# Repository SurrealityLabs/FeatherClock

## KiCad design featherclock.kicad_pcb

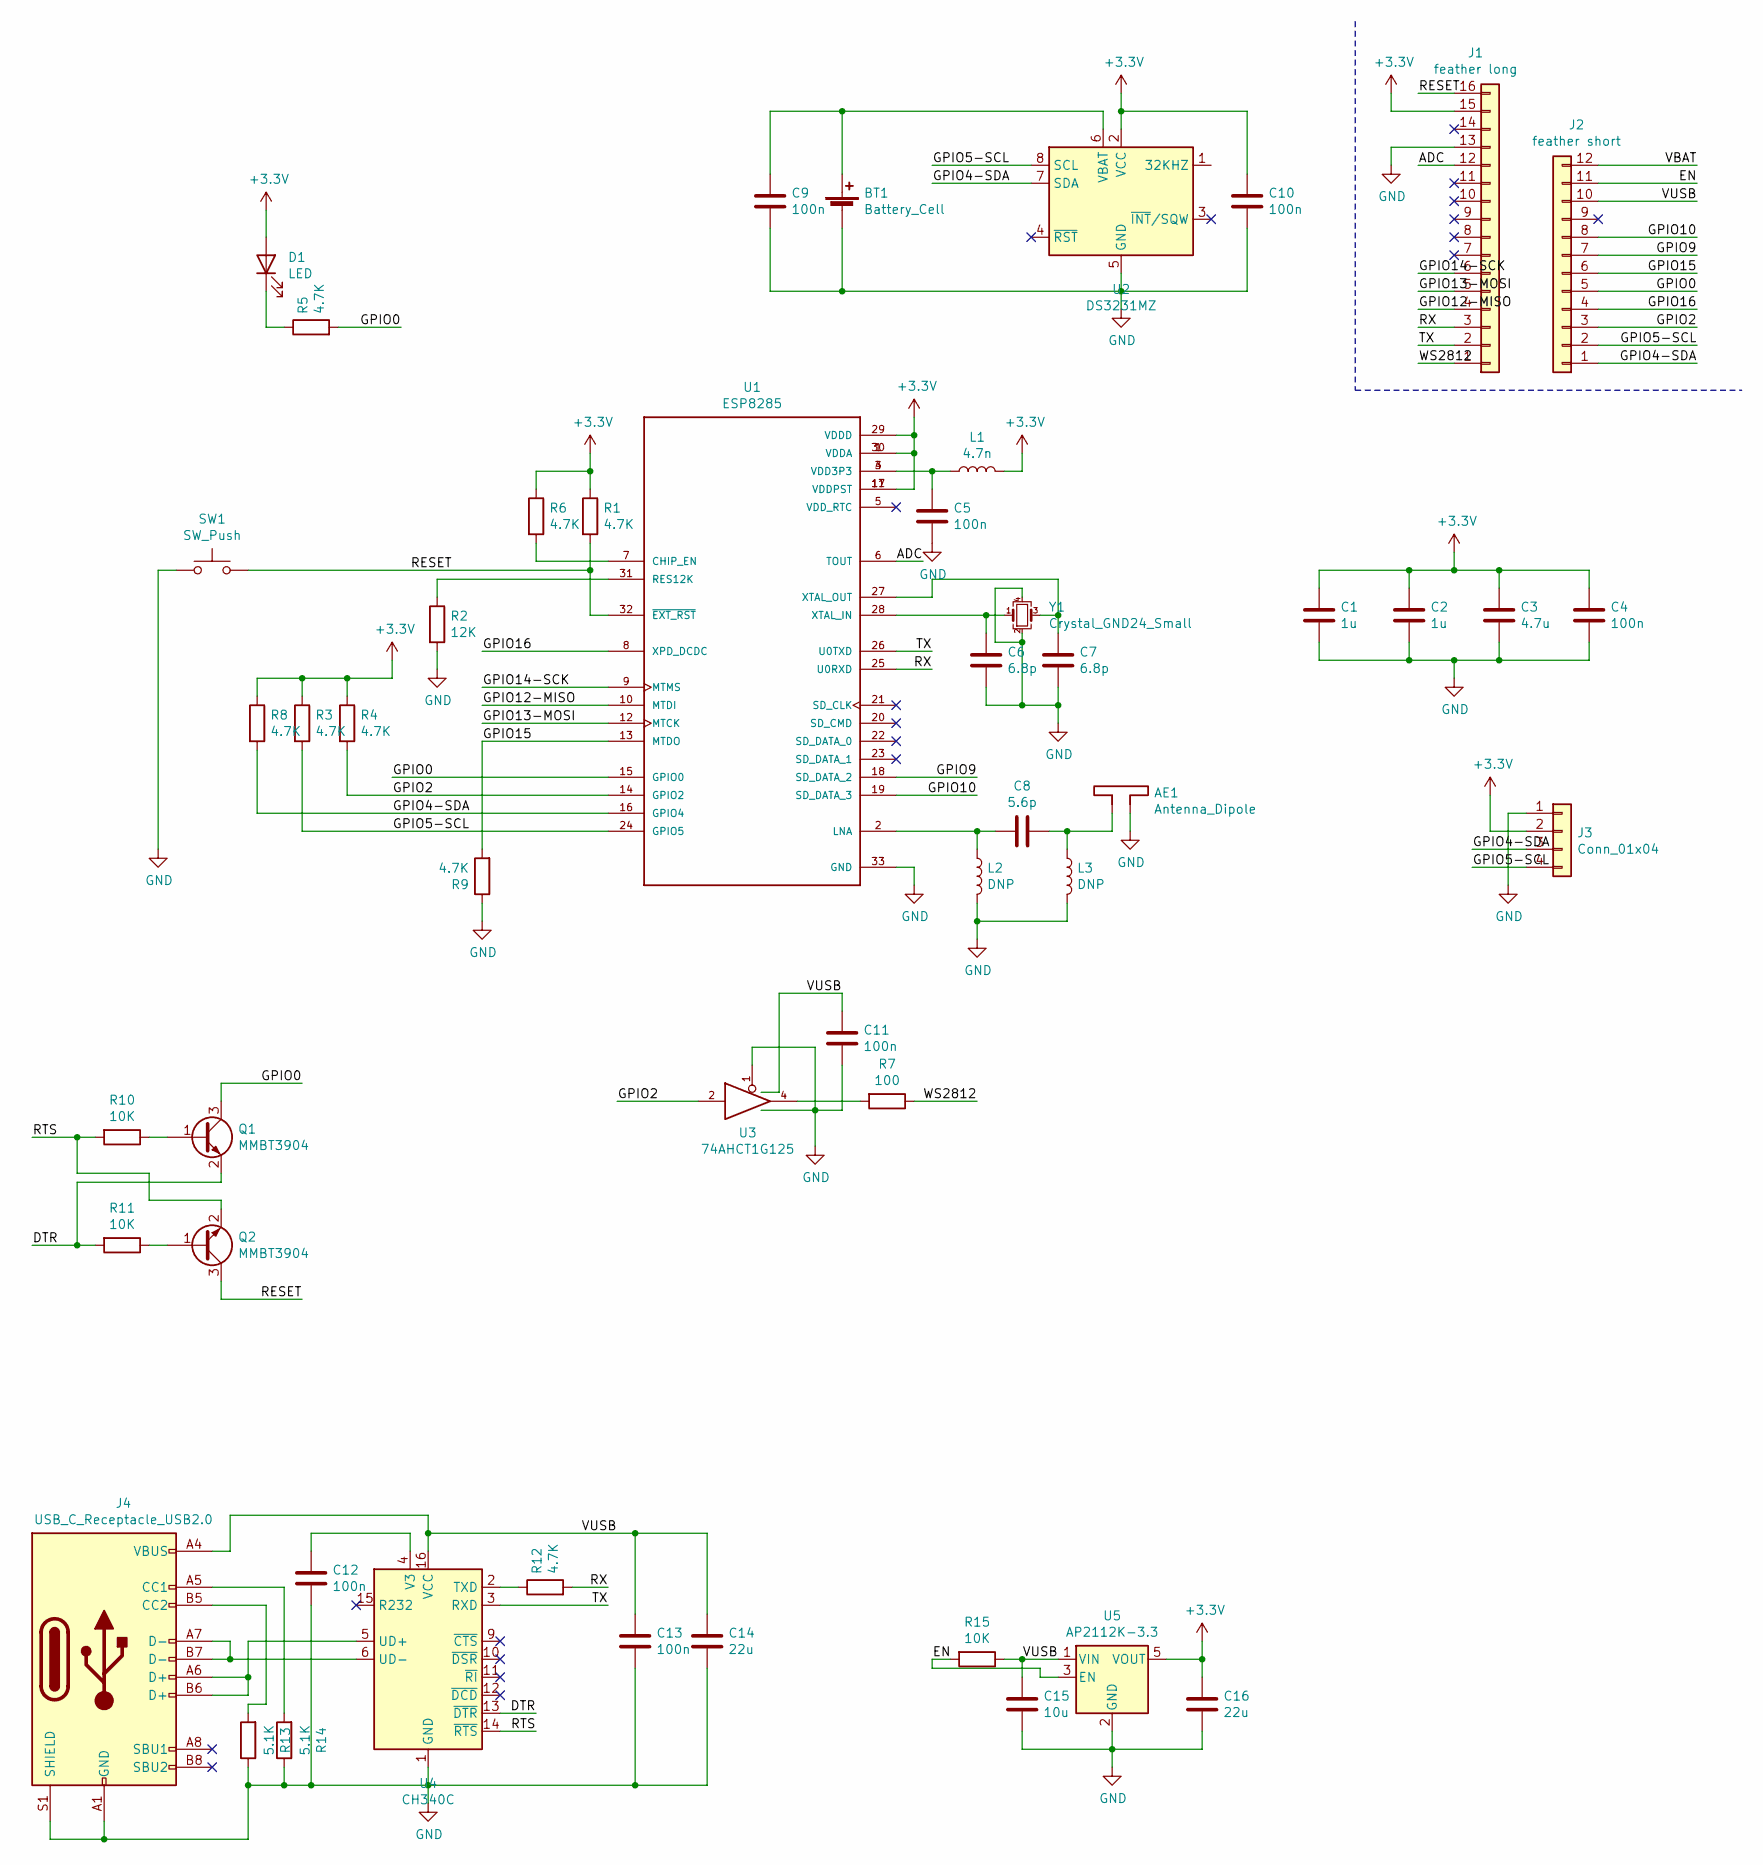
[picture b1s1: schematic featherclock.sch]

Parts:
AE1: Antenna_Dipole; Texas_SWRA117D_2.4GHz_Left
BT1: Battery_Cell; BAT_S8411-45R; LCSC C969906
C1, C2: 1u; C_0402_1005Metric; LCSC C52923
C3: 4.7u; C_0603_1608Metric; LCSC C19666
C4, C5, C9, C10, C11, C12, C13: 100n; C_0402_1005Metric; LCSC C1525
C6, C7: 6.8p; C_0402_1005Metric; LCSC C1576
C8: 5.6p; C_0402_1005Metric; LCSC C318596
C14, C16: 22u; C_0805_2012Metric; LCSC C45783
C15: 10u; C_0805_2012Metric; LCSC C15850
D1: LED; LED_0603; LCSC C72041
J1: feather long; PinHeader_1x16_P2.54mm_Vertical
J2: feather short; PinHeader_1x12_P2.54mm_Vertical
J3: Conn_01x04; JST_SH_SM04B-SRSS-TB_1x04-1MP_P1.00mm_Horizontal; LCSC C160404
J4: USB_C_Receptacle_USB2.0; USB_C_Receptacle_HRO_TYPE-C-31-M-12; LCSC C165948
L1: 4.7n; L_0402; LCSC C13595
L2, L3: DNP; L_0402
Q1, Q2: MMBT3904; SOT-23; LCSC C20526
R1, R3, R4, R5, R6, R8, R9, R12: 4.7K; R_0402_1005Metric; LCSC C25900
R2: 12K; R_0402_1005Metric; LCSC C25752
R7: 100; R_0402_1005Metric; LCSC C25076
R10, R11, R15: 10K; R_0402_1005Metric; LCSC C25744
R13, R14: 5.1K; R_0402_1005Metric; LCSC C25905
SW1: SW_Push; SW_SPST_TL3342; LCSC C318888
U1: ESP8285; QFN-32-1EP_5x5mm_Pitch0.5mm; LCSC C83901
U2: DS3231MZ; SOIC-8_3.9x4.9mm_P1.27mm; LCSC C107410
U3: 74AHCT1G125; SOT-353_SC-70-5; LCSC C12495
U4: CH340C; SOIC-16_3.9x9.9mm_P1.27mm; LCSC C84681
U5: AP2112K-3.3; SOT-23-5; LCSC C51118
Y1: Crystal_GND24_Small; Crystal_SMD_3225-4Pin_3.2x2.5mm; LCSC C23425

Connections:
+3V3: C1.1, C2.1, C3.1, C4.1, C10.1, C16.1, D1.2 (A), J1.15, J3.2, L1.2, R1.1, R3.1, R4.1, R6.1, R8.1, U1.1 (VDDA), U1.11 (VDDPST), U1.17 (VDDPST), U1.29 (VDDD), U1.30 (VDDA), U2.2 (VCC), U5.5 (VOUT)
/ADC: J1.12, U1.6 (TOUT)
/DTR: Q1.2 (E), R11.2, U4.13 (~DTR)
/EN: J2.11, R15.2, U5.3 (EN)
/GPIO0: J2.5, Q1.3 (C), R5.2, U1.15 (GPIO0)
/GPIO2: J2.3, R4.2, U1.14 (GPIO2), U3.2
/GPIO4-SDA: J2.1, J3.3, R8.2, U1.16 (GPIO4), U2.7 (SDA)
/GPIO5-SCL: J2.2, J3.4, R3.2, U1.24 (GPIO5), U2.8 (SCL)
/GPIO9: J2.7, U1.18 (SD_DATA_2)
/GPIO10: J2.8, U1.19 (SD_DATA_3)
/GPIO12-MISO: J1.4, U1.10 (MTDI)
/GPIO13-MOSI: J1.5, U1.12 (MTCK)
/GPIO14-SCK: J1.6, U1.9 (MTMS)
/GPIO15: J2.6, R9.2, U1.13 (MTDO)
/GPIO16: J2.4, U1.8 (XPD_DCDC)
/RESET: J1.16, Q2.3 (C), R1.2, SW1.2, U1.32 (~EXT_RST~)
/RTS: Q2.2 (E), R10.2, U4.14 (~RTS)
/RX: J1.3, R12.2, U1.25 (U0RXD)
/TX: J1.2, U1.26 (U0TXD), U4.3 (RXD)
/VBAT: J2.12
/WS2812: J1.1, R7.1
GND: AE1.2, BT1.2 (-), C1.2, C2.2, C3.2, C4.2, C5.2, C6.2, C7.2, C9.2, C10.2, C11.2, C12.2, C13.2, C14.2, C15.2, C16.2, J1.13, J3.1, J4.A1 (GND), J4.A12 (GND), J4.B1 (GND), J4.B12 (GND), J4.S1 (SHIELD), L2.2, L3.2, R2.2, R9.1, R13.1, R14.1, SW1.1, U1.33 (GND), U2.5 (GND), U3.1, U3.3 (GND), U4.1 (GND), U5.2 (GND), Y1.2, Y1.4
unnamed: AE1.1, C8.2, L3.1
unnamed: BT1.1 (+), C9.1, U2.6 (VBAT)
unnamed: C5.1, L1.1, U1.3 (VDD3P3), U1.4 (VDD3P3)
unnamed: C6.1, U1.28 (XTAL_IN), Y1.1
unnamed: C7.1, U1.27 (XTAL_OUT), Y1.3
unnamed: C8.1, L2.1, U1.2 (LNA)
unnamed: C12.1, U4.4 (V3)
unnamed: D1.1 (K), R5.1
unnamed: J4.A5 (CC1), R14.2
unnamed: J4.A6 (D+), J4.B6 (D+), U4.5 (UD+)
unnamed: J4.A7 (D-), J4.B7 (D-), U4.6 (UD-)
unnamed: J4.B5 (CC2), R13.2
unnamed: Q1.1 (B), R10.1
unnamed: Q2.1 (B), R11.1
unnamed: R2.1, U1.31 (RES12K)
unnamed: R6.2, U1.7 (CHIP_EN)
unnamed: R7.2, U3.4
unnamed: R12.1, U4.2 (TXD)
VCC: C11.1, C13.1, C14.1, C15.1, J2.10, J4.A4 (VBUS), J4.A9 (VBUS), J4.B4 (VBUS), J4.B9 (VBUS), R15.1, U3.5 (VCC), U4.16 (VCC), U5.1 (VIN)

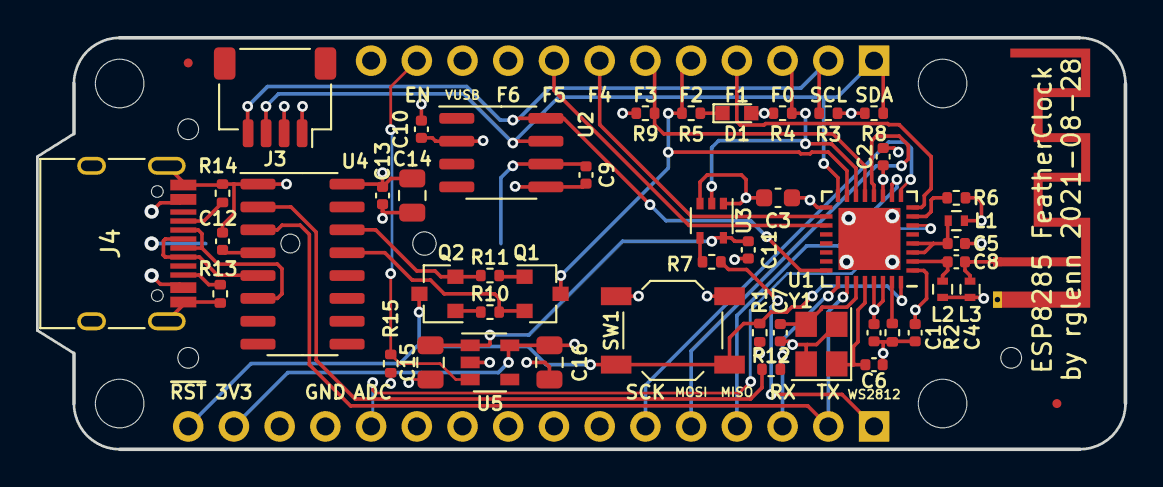
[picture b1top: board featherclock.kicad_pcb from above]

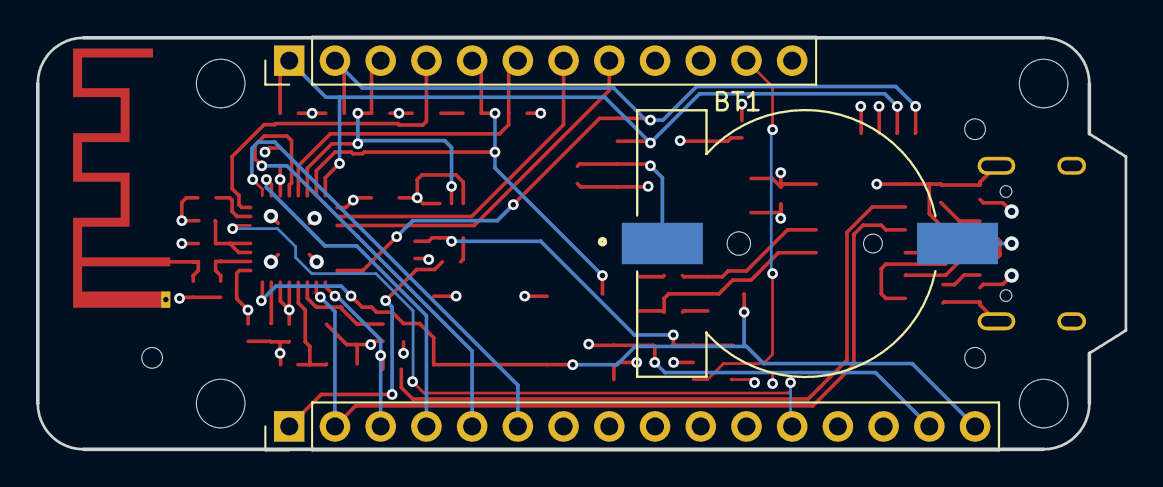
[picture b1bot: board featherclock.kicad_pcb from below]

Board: 4 copper layers, 60.4 x 22.9 mm, 50 parts (3 on the bottom side), 40 nets.

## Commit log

2021-08-13 Updated most 0603 packages to 0402
2021-08-14 Cleaned up for new 0402 parts, and rearranged parts now that we have so much space.
2021-08-14 Added tooling holes and fiducials. Extended board outline under USB connector. Ran DRC, looks good - can probably order these now.
2021-08-28 Adding ADC and enable pins
